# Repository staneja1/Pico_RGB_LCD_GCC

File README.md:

# Pico_RGB_LCD_GCC
PCB design for DIY rectangle controller

PCB Design done is KiCad 6.0, found in SuperPicoRect Folder

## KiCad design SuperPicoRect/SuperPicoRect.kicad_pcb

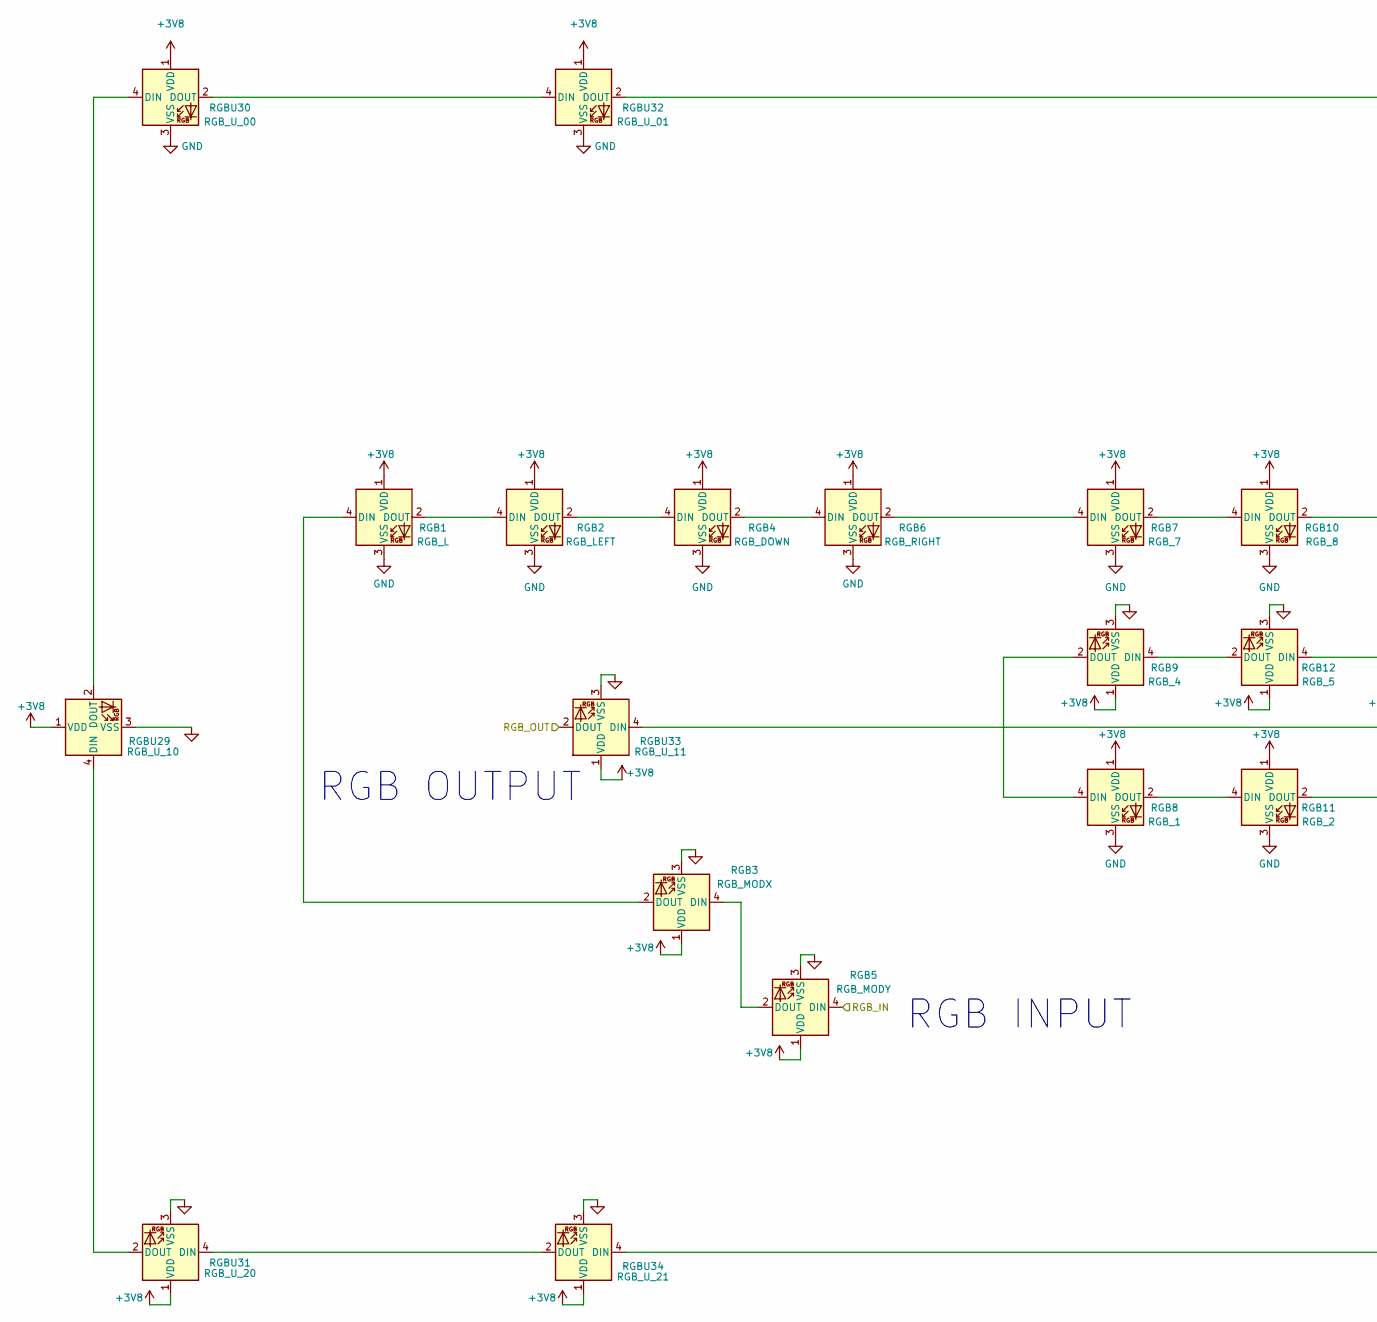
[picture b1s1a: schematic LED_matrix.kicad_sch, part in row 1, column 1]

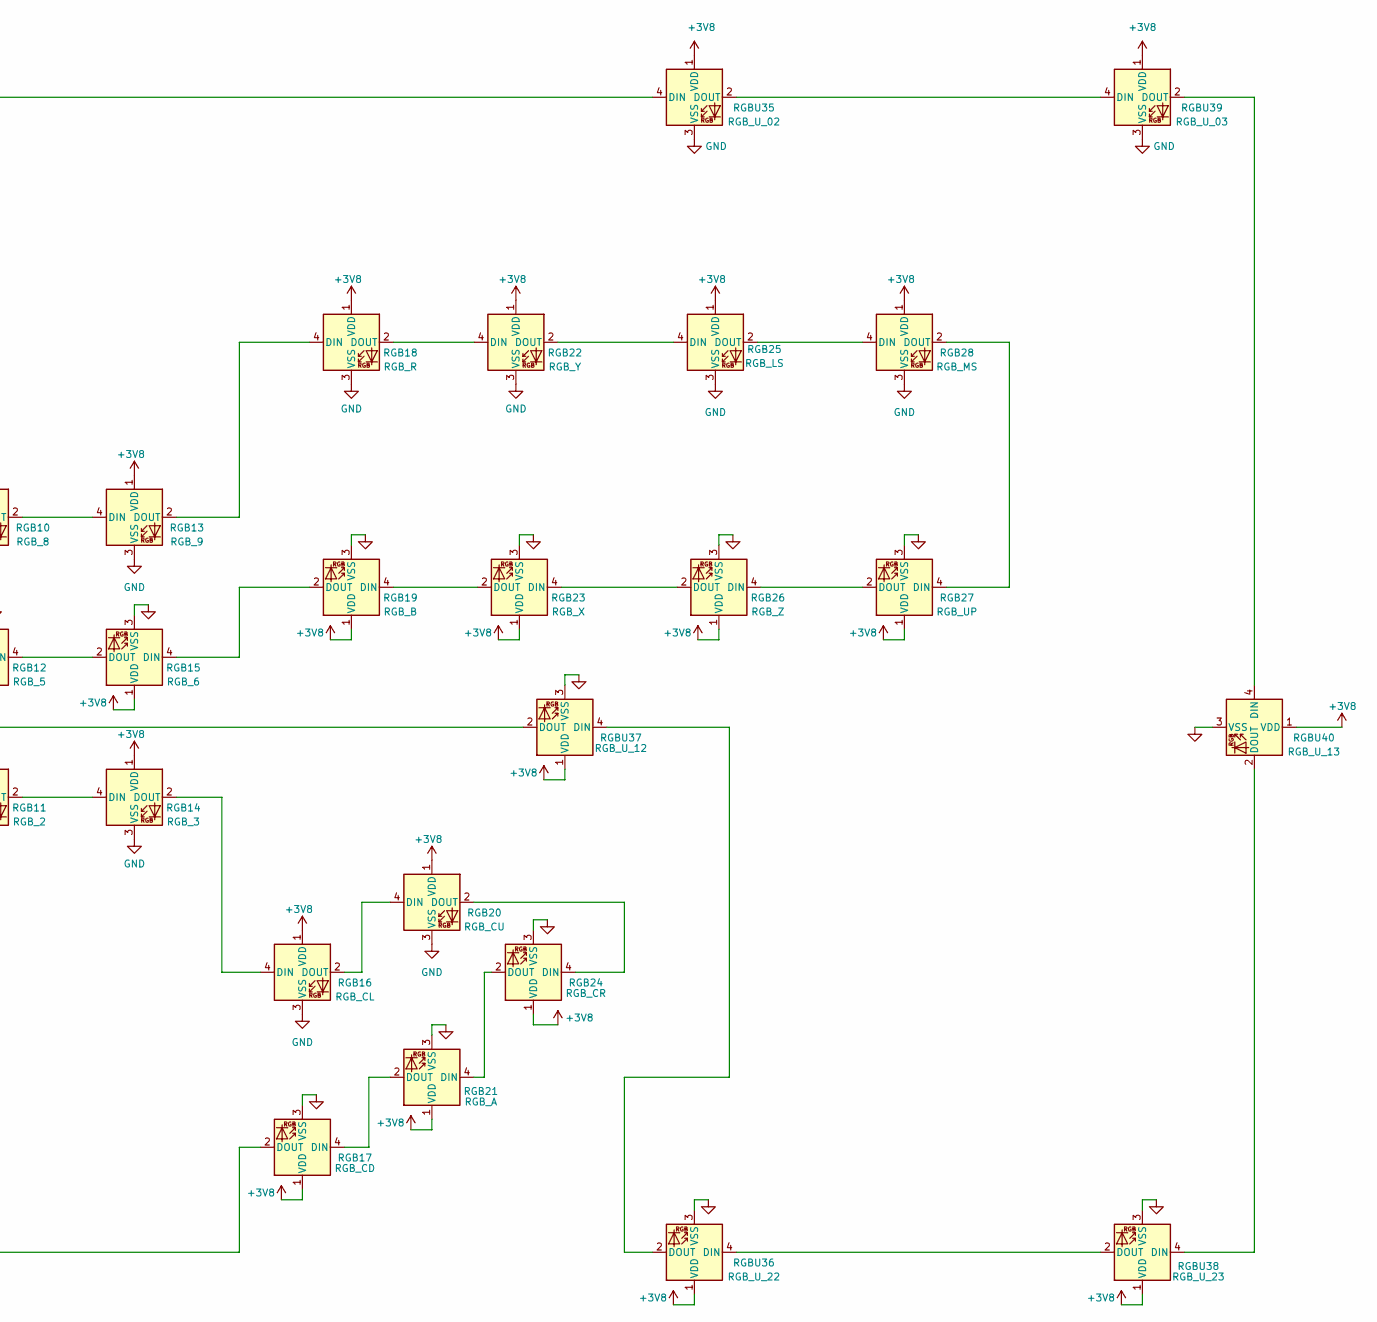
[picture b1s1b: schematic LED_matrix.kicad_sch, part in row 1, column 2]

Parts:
RGB1: RGB_L; LED_WS2812B_PLCC4_5.0x5.0mm_P3.2mm
RGB2: RGB_LEFT; LED_WS2812B_PLCC4_5.0x5.0mm_P3.2mm
RGB3: RGB_MODX; LED_WS2812B_PLCC4_5.0x5.0mm_P3.2mm
RGB4: RGB_DOWN; LED_WS2812B_PLCC4_5.0x5.0mm_P3.2mm
RGB5: RGB_MODY; LED_WS2812B_PLCC4_5.0x5.0mm_P3.2mm
RGB6: RGB_RIGHT; LED_WS2812B_PLCC4_5.0x5.0mm_P3.2mm
RGB7: RGB_7; LED_WS2812B_PLCC4_5.0x5.0mm_P3.2mm
RGB8: RGB_1; LED_WS2812B_PLCC4_5.0x5.0mm_P3.2mm
RGB9: RGB_4; LED_WS2812B_PLCC4_5.0x5.0mm_P3.2mm
RGB10: RGB_8; LED_WS2812B_PLCC4_5.0x5.0mm_P3.2mm
RGB11: RGB_2; LED_WS2812B_PLCC4_5.0x5.0mm_P3.2mm
RGB12: RGB_5; LED_WS2812B_PLCC4_5.0x5.0mm_P3.2mm
RGB13: RGB_9; LED_WS2812B_PLCC4_5.0x5.0mm_P3.2mm
RGB14: RGB_3; LED_WS2812B_PLCC4_5.0x5.0mm_P3.2mm
RGB15: RGB_6; LED_WS2812B_PLCC4_5.0x5.0mm_P3.2mm
RGB16: RGB_CL; LED_WS2812B_PLCC4_5.0x5.0mm_P3.2mm
RGB17: RGB_CD; LED_WS2812B_PLCC4_5.0x5.0mm_P3.2mm
RGB18: RGB_R; LED_WS2812B_PLCC4_5.0x5.0mm_P3.2mm
RGB19: RGB_B; LED_WS2812B_PLCC4_5.0x5.0mm_P3.2mm
RGB20: RGB_CU; LED_WS2812B_PLCC4_5.0x5.0mm_P3.2mm
RGB21: RGB_A; LED_WS2812B_PLCC4_5.0x5.0mm_P3.2mm
RGB22: RGB_Y; LED_WS2812B_PLCC4_5.0x5.0mm_P3.2mm
RGB23: RGB_X; LED_WS2812B_PLCC4_5.0x5.0mm_P3.2mm
RGB24: RGB_CR; LED_WS2812B_PLCC4_5.0x5.0mm_P3.2mm
RGB25: RGB_LS; LED_WS2812B_PLCC4_5.0x5.0mm_P3.2mm
RGB26: RGB_Z; LED_WS2812B_PLCC4_5.0x5.0mm_P3.2mm
RGB27: RGB_UP; LED_WS2812B_PLCC4_5.0x5.0mm_P3.2mm
RGB28: RGB_MS; LED_WS2812B_PLCC4_5.0x5.0mm_P3.2mm
RGBU29: RGB_U_10; LED_WS2812B_PLCC4_5.0x5.0mm_P3.2mm
RGBU30: RGB_U_00; LED_WS2812B_PLCC4_5.0x5.0mm_P3.2mm
RGBU31: RGB_U_20; LED_WS2812B_PLCC4_5.0x5.0mm_P3.2mm
RGBU32: RGB_U_01; LED_WS2812B_PLCC4_5.0x5.0mm_P3.2mm
RGBU33: RGB_U_11; LED_WS2812B_PLCC4_5.0x5.0mm_P3.2mm
RGBU34: RGB_U_21; LED_WS2812B_PLCC4_5.0x5.0mm_P3.2mm
RGBU35: RGB_U_02; LED_WS2812B_PLCC4_5.0x5.0mm_P3.2mm
RGBU36: RGB_U_22; LED_WS2812B_PLCC4_5.0x5.0mm_P3.2mm
RGBU37: RGB_U_12; LED_WS2812B_PLCC4_5.0x5.0mm_P3.2mm
RGBU38: RGB_U_23; LED_WS2812B_PLCC4_5.0x5.0mm_P3.2mm
RGBU39: RGB_U_03; LED_WS2812B_PLCC4_5.0x5.0mm_P3.2mm
RGBU40: RGB_U_13; LED_WS2812B_PLCC4_5.0x5.0mm_P3.2mm

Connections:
+3V8: RGB1.1 (VDD), RGB2.1 (VDD), RGB3.1 (VDD), RGB4.1 (VDD), RGB5.1 (VDD), RGB6.1 (VDD), RGB7.1 (VDD), RGB8.1 (VDD), RGB9.1 (VDD), RGB10.1 (VDD), RGB11.1 (VDD), RGB12.1 (VDD), RGB13.1 (VDD), RGB14.1 (VDD), RGB15.1 (VDD), RGB16.1 (VDD), RGB17.1 (VDD), RGB18.1 (VDD), RGB19.1 (VDD), RGB20.1 (VDD), RGB21.1 (VDD), RGB22.1 (VDD), RGB23.1 (VDD), RGB24.1 (VDD), RGB25.1 (VDD), RGB26.1 (VDD), RGB27.1 (VDD), RGB28.1 (VDD), RGBU29.1 (VDD), RGBU30.1 (VDD), RGBU31.1 (VDD), RGBU32.1 (VDD), RGBU33.1 (VDD), RGBU34.1 (VDD), RGBU35.1 (VDD), RGBU36.1 (VDD), RGBU37.1 (VDD), RGBU38.1 (VDD), RGBU39.1 (VDD), RGBU40.1 (VDD); also elsewhere on the board
/LED Matrix/RGB_OUT: RGBU33.2 (DOUT)
GND: RGB1.3 (VSS), RGB2.3 (VSS), RGB3.3 (VSS), RGB4.3 (VSS), RGB5.3 (VSS), RGB6.3 (VSS), RGB7.3 (VSS), RGB8.3 (VSS), RGB9.3 (VSS), RGB10.3 (VSS), RGB11.3 (VSS), RGB12.3 (VSS), RGB13.3 (VSS), RGB14.3 (VSS), RGB15.3 (VSS), RGB16.3 (VSS), RGB17.3 (VSS), RGB18.3 (VSS), RGB19.3 (VSS), RGB20.3 (VSS), RGB21.3 (VSS), RGB22.3 (VSS), RGB23.3 (VSS), RGB24.3 (VSS), RGB25.3 (VSS), RGB26.3 (VSS), RGB27.3 (VSS), RGB28.3 (VSS), RGBU29.3 (VSS), RGBU30.3 (VSS), RGBU31.3 (VSS), RGBU32.3 (VSS), RGBU33.3 (VSS), RGBU34.3 (VSS), RGBU35.3 (VSS), RGBU36.3 (VSS), RGBU37.3 (VSS), RGBU38.3 (VSS), RGBU39.3 (VSS), RGBU40.3 (VSS); also elsewhere on the board
GPIO18: RGB5.4 (DIN); also elsewhere on the board
unnamed: RGB1.2 (DOUT), RGB2.4 (DIN)
unnamed: RGB1.4 (DIN), RGB3.2 (DOUT)
unnamed: RGB4.2 (DOUT), RGB6.4 (DIN)
unnamed: RGB2.2 (DOUT), RGB4.4 (DIN)
unnamed: RGB3.4 (DIN), RGB5.2 (DOUT)
unnamed: RGB6.2 (DOUT), RGB7.4 (DIN)
unnamed: RGB8.4 (DIN), RGB9.2 (DOUT)
unnamed: RGB10.2 (DOUT), RGB13.4 (DIN)
unnamed: RGB7.2 (DOUT), RGB10.4 (DIN)
unnamed: RGB8.2 (DOUT), RGB11.4 (DIN)
unnamed: RGB9.4 (DIN), RGB12.2 (DOUT)
unnamed: RGB11.2 (DOUT), RGB14.4 (DIN)
unnamed: RGB12.4 (DIN), RGB15.2 (DOUT)
unnamed: RGB16.2 (DOUT), RGB20.4 (DIN)
unnamed: RGB14.2 (DOUT), RGB16.4 (DIN)
unnamed 78: RGB17.4 (DIN), RGB21.2 (DOUT); also elsewhere on the board
unnamed: RGB13.2 (DOUT), RGB18.4 (DIN)
unnamed: RGB15.4 (DIN), RGB19.2 (DOUT)
unnamed: RGB20.2 (DOUT), RGB24.4 (DIN)
unnamed: RGB22.2 (DOUT), RGB25.4 (DIN)
unnamed: RGB18.2 (DOUT), RGB22.4 (DIN)
unnamed: RGB19.4 (DIN), RGB23.2 (DOUT)
unnamed: RGB23.4 (DIN), RGB26.2 (DOUT)
unnamed: RGB21.4 (DIN), RGB24.2 (DOUT)
unnamed: RGB25.2 (DOUT), RGB28.4 (DIN)
unnamed: RGB26.4 (DIN), RGB27.2 (DOUT)
unnamed: RGB27.4 (DIN), RGB28.2 (DOUT)
unnamed: RGBU29.4 (DIN), RGBU31.2 (DOUT)
unnamed: RGBU30.2 (DOUT), RGBU32.4 (DIN)
unnamed: RGBU29.2 (DOUT), RGBU30.4 (DIN)
unnamed: RGBU31.4 (DIN), RGBU34.2 (DOUT)
unnamed: RGBU32.2 (DOUT), RGBU35.4 (DIN)
unnamed: RGBU33.4 (DIN), RGBU37.2 (DOUT)
unnamed 96: RGB17.2 (DOUT), RGBU34.4 (DIN); also elsewhere on the board
unnamed: RGBU36.2 (DOUT), RGBU37.4 (DIN)
unnamed: RGBU36.4 (DIN), RGBU38.2 (DOUT)
unnamed: RGBU38.4 (DIN), RGBU40.2 (DOUT)
unnamed: RGBU39.2 (DOUT), RGBU40.4 (DIN)
unnamed: RGBU35.2 (DOUT), RGBU39.4 (DIN)

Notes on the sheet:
RGB OUTPUT
RGB INPUT

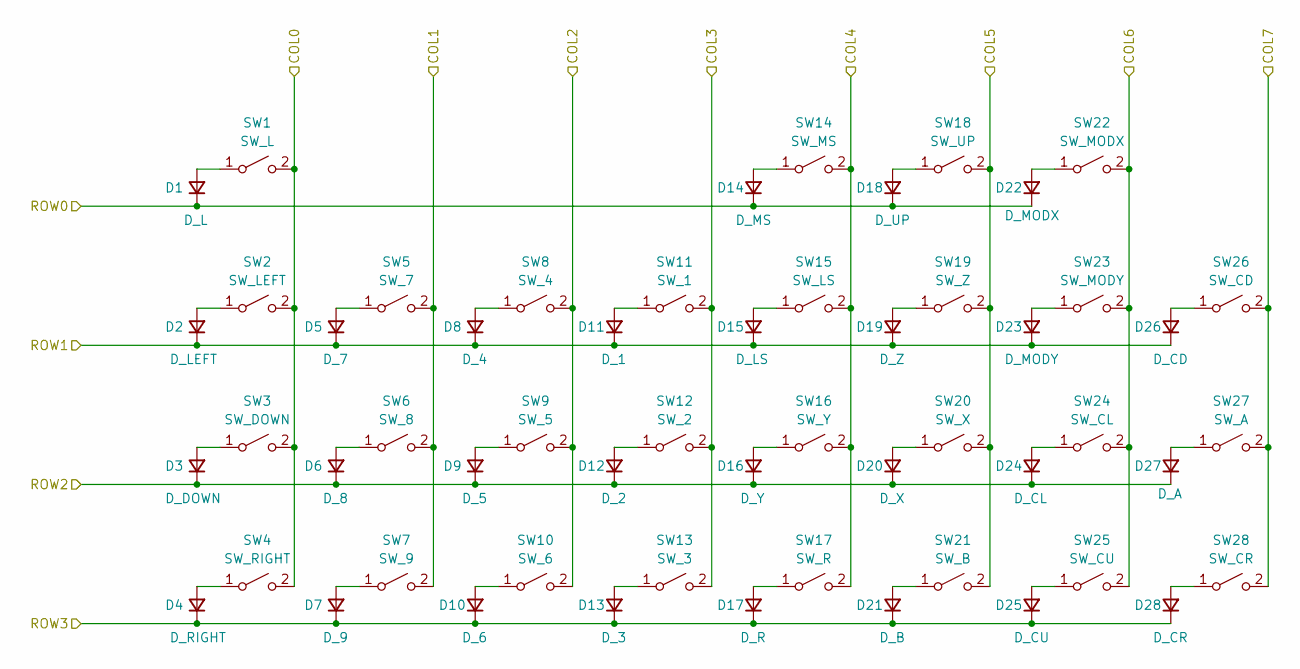
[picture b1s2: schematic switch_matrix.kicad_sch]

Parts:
D1: D_L; D_SOD-123
D2: D_LEFT; D_SOD-123
D3: D_DOWN; D_SOD-123
D4: D_RIGHT; D_SOD-123
D5: D_7; D_SOD-123
D6: D_8; D_SOD-123
D7: D_9; D_SOD-123
D8: D_4; D_SOD-123
D9: D_5; D_SOD-123
D10: D_6; D_SOD-123
D11: D_1; D_SOD-123
D12: D_2; D_SOD-123
D13: D_3; D_SOD-123
D14: D_MS; D_SOD-123
D15: D_LS; D_SOD-123
D16: D_Y; D_SOD-123
D17: D_R; D_SOD-123
D18: D_UP; D_SOD-123
D19: D_Z; D_SOD-123
D20: D_X; D_SOD-123
D21: D_B; D_SOD-123
D22: D_MODX; D_SOD-123
D23: D_MODY; D_SOD-123
D24: D_CL; D_SOD-123
D25: D_CU; D_SOD-123
D26: D_CD; D_SOD-123
D27: D_A; D_SOD-123
D28: D_CR; D_SOD-123
SW1: SW_L; SW_Hotswap_Kailh_MX_plated_1.00u
SW2: SW_LEFT; SW_Hotswap_Kailh_MX_plated_1.00u
SW3: SW_DOWN; SW_Hotswap_Kailh_MX_plated_1.00u
SW4: SW_RIGHT; SW_Hotswap_Kailh_MX_plated_1.00u
SW5: SW_7; SW_Hotswap_Kailh_MX_plated_1.00u
SW6: SW_8; SW_Hotswap_Kailh_MX_plated_1.00u
SW7: SW_9; SW_Hotswap_Kailh_MX_plated_1.00u
SW8: SW_4; SW_Hotswap_Kailh_MX_plated_1.00u
SW9: SW_5; SW_Hotswap_Kailh_MX_plated_1.00u
SW10: SW_6; SW_Hotswap_Kailh_MX_plated_1.00u
SW11: SW_1; SW_Hotswap_Kailh_MX_plated_1.00u
SW12: SW_2; SW_Hotswap_Kailh_MX_plated_1.00u
SW13: SW_3; SW_Hotswap_Kailh_MX_plated_1.00u
SW14: SW_MS; SW_Hotswap_Kailh_MX_plated_1.00u
SW15: SW_LS; SW_Hotswap_Kailh_MX_plated_1.00u
SW16: SW_Y; SW_Hotswap_Kailh_MX_plated_1.00u
SW17: SW_R; SW_Hotswap_Kailh_MX_plated_1.00u
SW18: SW_UP; SW_Hotswap_Kailh_MX_plated_1.00u
SW19: SW_Z; SW_Hotswap_Kailh_MX_plated_1.00u
SW20: SW_X; SW_Hotswap_Kailh_MX_plated_1.00u
SW21: SW_B; SW_Hotswap_Kailh_MX_plated_1.00u
SW22: SW_MODX; SW_Hotswap_Kailh_MX_plated_1.00u
SW23: SW_MODY; SW_Hotswap_Kailh_MX_plated_1.00u
SW24: SW_CL; SW_Hotswap_Kailh_MX_plated_1.00u
SW25: SW_CU; SW_Hotswap_Kailh_MX_plated_1.00u
SW26: SW_CD; SW_Hotswap_Kailh_MX_plated_1.00u
SW27: SW_A; SW_Hotswap_Kailh_MX_plated_1.00u
SW28: SW_CR; SW_Hotswap_Kailh_MX_plated_1.00u

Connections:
GPIO0: SW26.2 (B), SW27.2 (B), SW28.2 (B); also elsewhere on the board
GPIO1: SW22.2 (B), SW23.2 (B), SW24.2 (B), SW25.2 (B); also elsewhere on the board
GPIO2: SW18.2 (B), SW19.2 (B), SW20.2 (B), SW21.2 (B); also elsewhere on the board
GPIO3: SW14.2 (B), SW15.2 (B), SW16.2 (B), SW17.2 (B); also elsewhere on the board
GPIO4: SW11.2 (B), SW12.2 (B), SW13.2 (B); also elsewhere on the board
GPIO5: SW8.2 (B), SW9.2 (B), SW10.2 (B); also elsewhere on the board
GPIO7: SW1.2 (B), SW2.2 (B), SW3.2 (B), SW4.2 (B); also elsewhere on the board
GPIO19: D4.1 (K), D7.1 (K), D10.1 (K), D13.1 (K), D17.1 (K), D21.1 (K), D25.1 (K), D28.1 (K); also elsewhere on the board
GPIO20: D3.1 (K), D6.1 (K), D9.1 (K), D12.1 (K), D16.1 (K), D20.1 (K), D24.1 (K), D27.1 (K); also elsewhere on the board
GPIO21: D2.1 (K), D5.1 (K), D8.1 (K), D11.1 (K), D15.1 (K), D19.1 (K), D23.1 (K), D26.1 (K); also elsewhere on the board
GPIO22: D1.1 (K), D14.1 (K), D18.1 (K), D22.1 (K); also elsewhere on the board
unnamed: D1.2 (A), SW1.1 (A)
unnamed: D2.2 (A), SW2.1 (A)
unnamed: D3.2 (A), SW3.1 (A)
unnamed: D4.2 (A), SW4.1 (A)
unnamed 36: D5.2 (A), SW5.1 (A); also elsewhere on the board
unnamed 37: D6.2 (A), SW6.1 (A); also elsewhere on the board
unnamed 38: D7.2 (A), SW7.1 (A); also elsewhere on the board
unnamed: D8.2 (A), SW8.1 (A)
unnamed: D9.2 (A), SW9.1 (A)
unnamed: D10.2 (A), SW10.1 (A)
unnamed: D11.2 (A), SW11.1 (A)
unnamed: D12.2 (A), SW12.1 (A)
unnamed: D13.2 (A), SW13.1 (A)
unnamed: D14.2 (A), SW14.1 (A)
unnamed: D15.2 (A), SW15.1 (A)
unnamed: D16.2 (A), SW16.1 (A)
unnamed: D17.2 (A), SW17.1 (A)
unnamed: D18.2 (A), SW18.1 (A)
unnamed: D19.2 (A), SW19.1 (A)
unnamed: D20.2 (A), SW20.1 (A)
unnamed: D21.2 (A), SW21.1 (A)
unnamed 53: D22.2 (A), SW22.1 (A); also elsewhere on the board
unnamed 54: D23.2 (A), SW23.1 (A); also elsewhere on the board
unnamed: D24.2 (A), SW24.1 (A)
unnamed: D25.2 (A), SW25.1 (A)
unnamed: D26.2 (A), SW26.1 (A)
unnamed: D27.2 (A), SW27.1 (A)
unnamed: D28.2 (A), SW28.1 (A)
unnamed: SW5.2 (B), SW6.2 (B), SW7.2 (B)

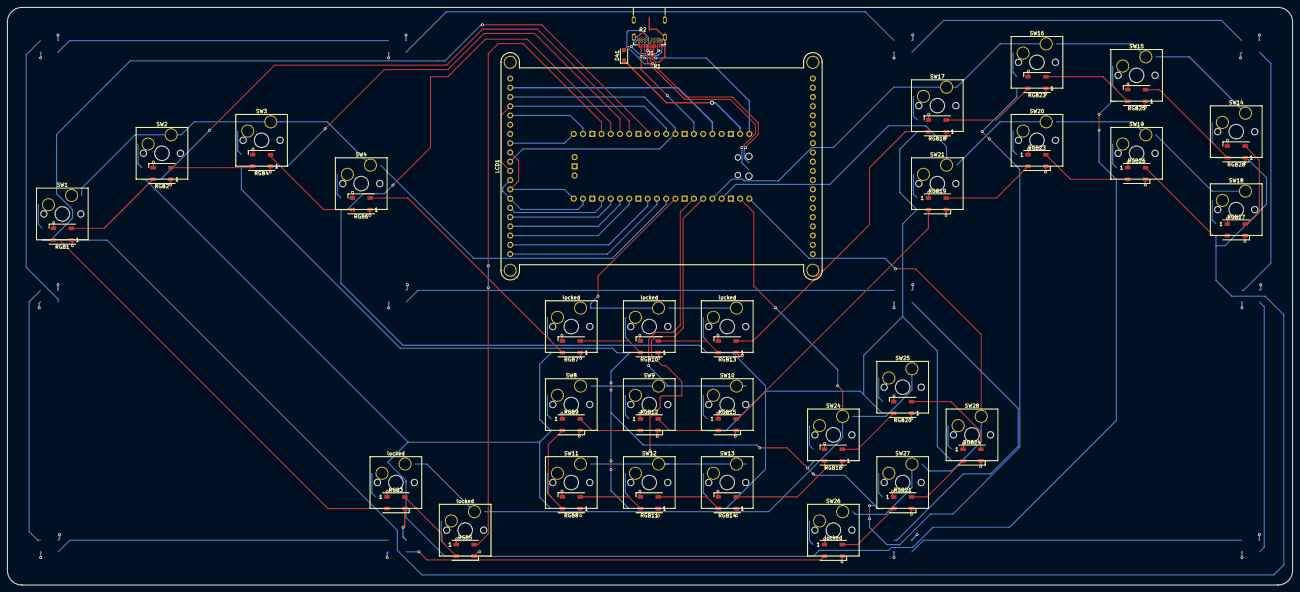
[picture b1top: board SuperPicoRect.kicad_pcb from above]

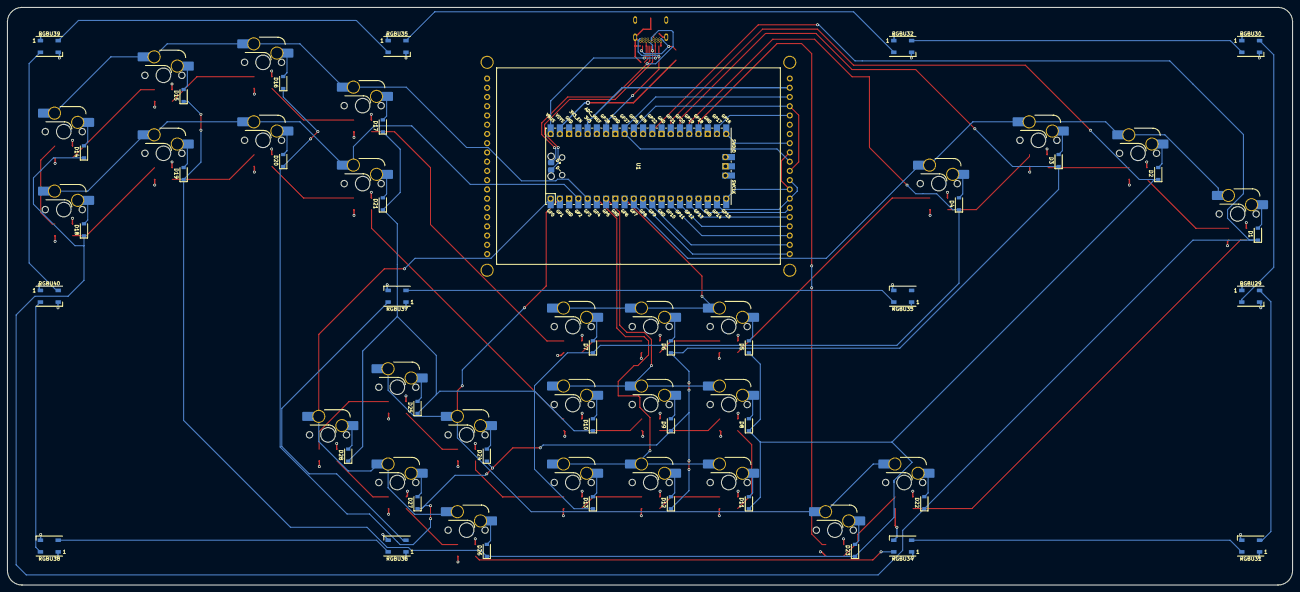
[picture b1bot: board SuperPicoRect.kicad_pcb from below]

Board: 4 copper layers, 353.2 x 158.8 mm, 102 parts (41 on the bottom side), 102 nets.

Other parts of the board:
D41: MBR1020VL; D_SOD-123F
J1: SS-52400-003; BELFUSE_SS-52400-003
LCD1: Adafruit_3.2_TFT_320x240; Adafruit TFT 3.2 320x240
R1, R2: 5.1k R; R_0201_0603Metric
U1: Pico; RPi_Pico_SMD_TH
locked: locked; SW_Hotswap_Kailh_MX_plated_1.00u
locked#2, locked#5, locked#6: locked; SW_Hotswap_Kailh_MX_plated_1.00u
locked#3: SW_MODY; SW_Hotswap_Kailh_MX_plated_1.00u
locked#4: RGB_CD; LED_WS2812B_PLCC4_5.0x5.0mm_P3.2mm

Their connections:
+3V3: LCD1.22 (+5V), U1.36 (3V3)
+3V8: D41.1 (K), U1.39 (VSYS), locked#4.1 (VDD); also elsewhere on the board
D+: J1.A6 (DP1), J1.B6 (DP2), U1.45 (D+)
D-: J1.A7 (DN1), J1.B7 (DN2), U1.44 (D-)
GND: J1.A1 (GNDA1), J1.A12 (GNDA2), J1.B1 (GNDB1), J1.B12 (GNDB2), J1.G1 (GND/SHIELD), J1.G2 (GND/SHIELD), J1.G3 (GND/SHIELD), J1.G4 (GND/SHIELD), J1.S1 (GND/SHIELD), J1.S2 (GND/SHIELD), J1.S3 (GND/SHIELD), J1.S4 (GND/SHIELD), LCD1.21 (GND), R1.1, R2.1, U1.3 (GND), U1.8 (GND), U1.13 (GND), U1.18 (GND), U1.23 (GND), U1.28 (GND), U1.33 (AGND), U1.38 (GND), U1.42 (GND), locked#4.3 (VSS); also elsewhere on the board
GPIO0: U1.1 (GPIO0); also elsewhere on the board
GPIO1: U1.2 (GPIO1), locked.2 (B), locked#3.2 (B); also elsewhere on the board
GPIO2: U1.4 (GPIO2); also elsewhere on the board
GPIO3: U1.5 (GPIO3); also elsewhere on the board
GPIO4: U1.6 (GPIO4); also elsewhere on the board
GPIO5: U1.7 (GPIO5); also elsewhere on the board
GPIO6: U1.9 (GPIO6), locked#2.2 (B), locked#5.2 (B), locked#6.2 (B)
GPIO7: U1.10 (GPIO7); also elsewhere on the board
GPIO8: LCD1.40 (LCD_DATA7_5V), U1.11 (GPIO8)
GPIO9: LCD1.39 (LCD_DATA6_5V), U1.12 (GPIO9)
GPIO10: LCD1.38 (LCD_DATA5_5V), U1.14 (GPIO10)
GPIO11: LCD1.37 (LCD_DATA4_5V), U1.15 (GPIO11)
GPIO12: LCD1.36 (LCD_DATA3_5V), U1.16 (GPIO12)
GPIO13: LCD1.35 (LCD_DATA2_5V), U1.17 (GPIO13)
GPIO14: LCD1.32 (LCD_Y-), LCD1.34 (LCD_DATA1_5V), U1.19 (GPIO14)
GPIO15: LCD1.29 (LCD_X+), LCD1.33 (LCD_DATA0_5V), U1.20 (GPIO15)
GPIO16: LCD1.28 (LCD_LITE), U1.21 (GPIO16)
GPIO17: LCD1.25 (LCD_WR_5V), U1.22 (GPIO17)
GPIO18: U1.24 (GPIO18); also elsewhere on the board
GPIO19: U1.25 (GPIO19); also elsewhere on the board
GPIO20: U1.26 (GPIO20); also elsewhere on the board
GPIO21: U1.27 (GPIO21); also elsewhere on the board
GPIO22: U1.29 (GPIO22); also elsewhere on the board
GPIO26: LCD1.24 (LCD_RS_5V), LCD1.31 (LCD_X-), U1.31 (GPIO26_ADC0)
GPIO27: LCD1.23 (LCD_CS_5V), LCD1.30 (LCD_Y+), U1.32 (GPIO27_ADC1)
GPIO28: J1.A11 (SSRXP2), J1.B11 (SSRXP1), U1.34 (GPIO28_ADC2)
unnamed 36: locked#2.1 (A); also elsewhere on the board
unnamed 37: locked#6.1 (A); also elsewhere on the board
unnamed 38: locked#5.1 (A); also elsewhere on the board
unnamed 53: locked.1 (A); also elsewhere on the board
unnamed 54: locked#3.1 (A); also elsewhere on the board
unnamed: D41.2 (A), J1.A2 (SSTXP1), J1.B2 (SSTXP2)
unnamed: J1.A5 (CC1), R1.2
unnamed: J1.B5 (CC2), R2.2
unnamed 78: locked#4.4 (DIN); also elsewhere on the board
unnamed 96: locked#4.2 (DOUT); also elsewhere on the board
VBUS: J1.A4 (VBUSA1), J1.A9 (VBUSA2), J1.B4 (VBUSB1), J1.B9 (VBUSB2), U1.40 (VBUS)

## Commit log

2023-01-03 Add kicad library submodules
2023-01-16 First Full Assembly, pre-review
2023-01-16 File cleanup
